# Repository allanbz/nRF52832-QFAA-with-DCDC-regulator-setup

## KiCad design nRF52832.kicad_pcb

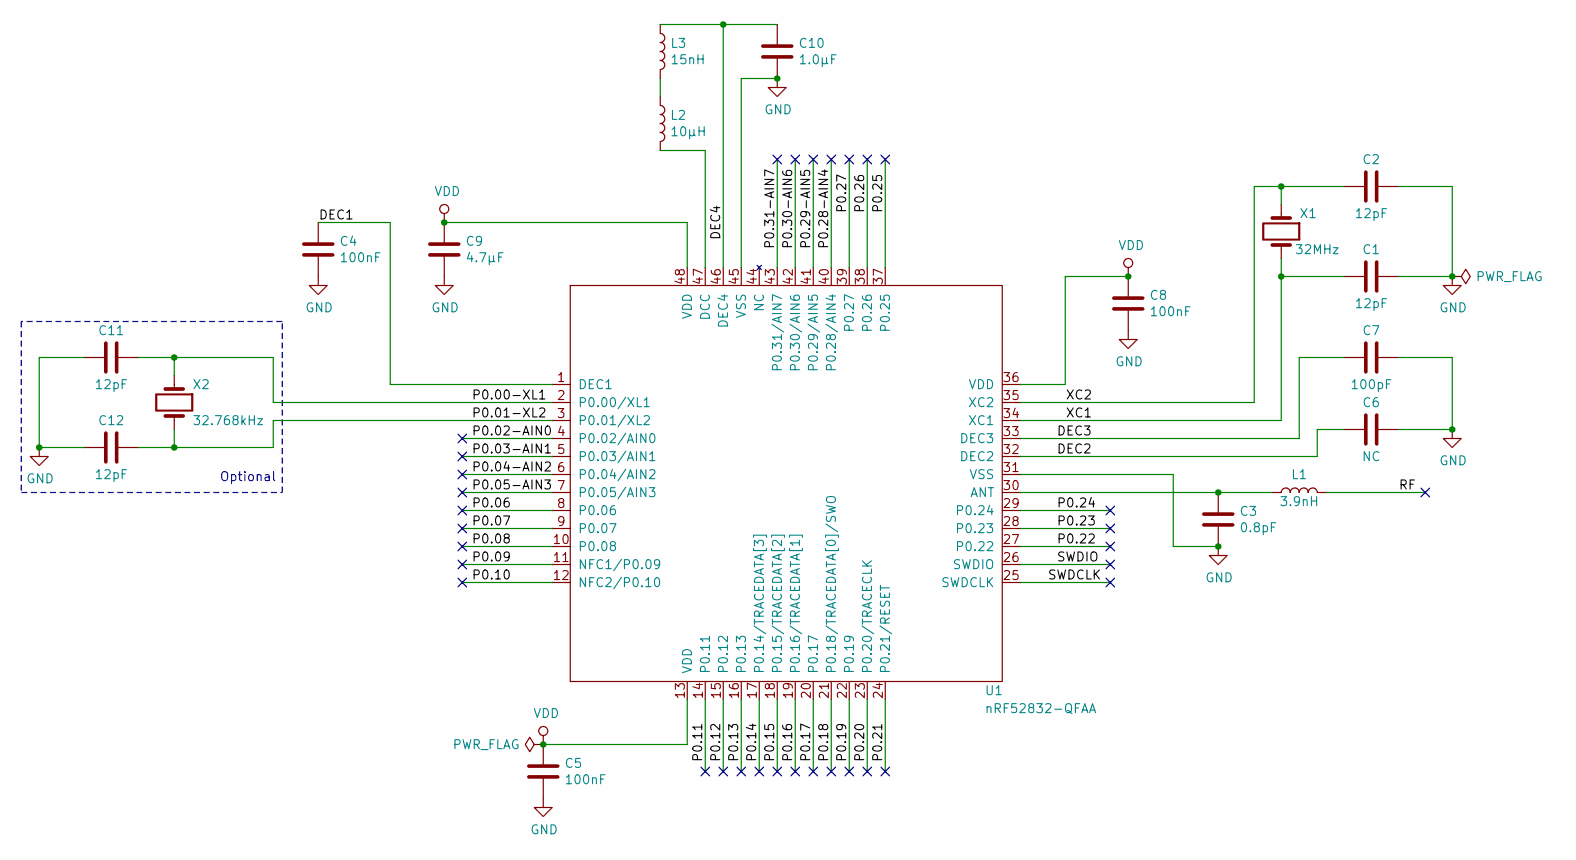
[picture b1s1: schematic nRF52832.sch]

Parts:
C1, C2, C11, C12: 12pF; C_0402_1005Metric
C3: 0.8pF; C_0402_1005Metric
C4, C5, C8: 100nF; C_0402_1005Metric
C6: NC; C_0402_1005Metric
C7: 100pF; C_0402_1005Metric
C9: 4.7µF; C_0603_1608Metric
C10: 1.0µF; C_0603_1608Metric
L1: 3.9nH; L_0402_1005Metric
L2: 10µH; L_0603_1608Metric
L3: 15nH; L_0402_1005Metric
U1: nRF52832-QFAA; QFN-48-1EP_6x6mm_P0.4mm_EP4.2x4.2mm
X1: 32MHz; Crystal_SMD_2016-4Pin_2.0x1.6mm
X2: 32.768kHz; Crystal_SMD_3215-2Pin_3.2x1.5mm

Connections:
/DEC1: C4.1, U1.1 (DEC1)
/DEC2: C6.2, U1.32 (DEC2)
/DEC3: C7.2, U1.33 (DEC3)
/DEC4: C10.1, L3.1, U1.46 (DEC4)
/P0.00-XL1: C11.1, U1.2 (P0.00/XL1), X2.1
/P0.01-XL2: C12.1, U1.3 (P0.01/XL2), X2.2
/P0.02-AIN0: U1.4 (P0.02/AIN0)
/P0.03-AIN1: U1.5 (P0.03/AIN1)
/P0.04-AIN2: U1.6 (P0.04/AIN2)
/P0.05-AIN3: U1.7 (P0.05/AIN3)
/P0.06: U1.8 (P0.06)
/P0.07: U1.9 (P0.07)
/P0.08: U1.10 (P0.08)
/P0.09: U1.11 (NFC1/P0.09)
/P0.10: U1.12 (NFC2/P0.10)
/P0.11: U1.14 (P0.11)
/P0.12: U1.15 (P0.12)
/P0.13: U1.16 (P0.13)
/P0.14: U1.17 (P0.14/TRACEDATA[3])
/P0.15: U1.18 (P0.15/TRACEDATA[2])
/P0.16: U1.19 (P0.16/TRACEDATA[1])
/P0.17: U1.20 (P0.17)
/P0.18: U1.21 (P0.18/TRACEDATA[0]/SWO)
/P0.19: U1.22 (P0.19)
/P0.20: U1.23 (P0.20/TRACECLK)
/P0.21: U1.24 (P0.21/RESET)
/P0.22: U1.27 (P0.22)
/P0.23: U1.28 (P0.23)
/P0.24: U1.29 (P0.24)
/P0.25: U1.37 (P0.25)
/P0.26: U1.38 (P0.26)
/P0.27: U1.39 (P0.27)
/P0.28-AIN4: U1.40 (P0.28/AIN4)
/P0.29-AIN5: U1.41 (P0.29/AIN5)
/P0.30-AIN6: U1.42 (P0.30/AIN6)
/P0.31-AIN7: U1.43 (P0.31/AIN7)
/RF: L1.1
/SWDCLK: U1.25 (SWDCLK)
/SWDIO: U1.26 (SWDIO)
/XC1: C1.2, U1.34 (XC1), X1.2
/XC2: C2.2, U1.35 (XC2), X1.1
GND: C1.1, C2.1, C3.2, C4.2, C5.2, C6.1, C7.1, C8.2, C9.2, C10.2, C11.2, C12.2, U1.31 (VSS), U1.45 (VSS), U1.49
unnamed: C3.1, L1.2, U1.30 (ANT)
unnamed: L2.1, L3.2
unnamed: L2.2, U1.47 (DCC)
VDD: C5.1, C8.1, C9.1, U1.13 (VDD), U1.36 (VDD), U1.48 (VDD)

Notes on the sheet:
Optional

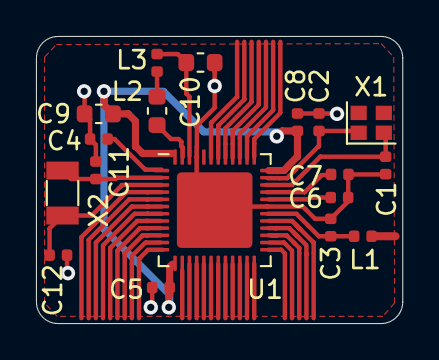
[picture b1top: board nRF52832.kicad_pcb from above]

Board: 2 copper layers, 20.4 x 16.0 mm, 18 parts (0 on the bottom side), 13 nets.

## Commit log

2019-06-03 Schematic
2019-06-10 PCB Design
2019-06-10 Adding RF track
